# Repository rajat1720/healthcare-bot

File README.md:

# healthcare-bot
A bot that can record the temperature of every individual and send it to the doctors, so that they can filtrate the people who needs to go for the second level of testing for Covid-19

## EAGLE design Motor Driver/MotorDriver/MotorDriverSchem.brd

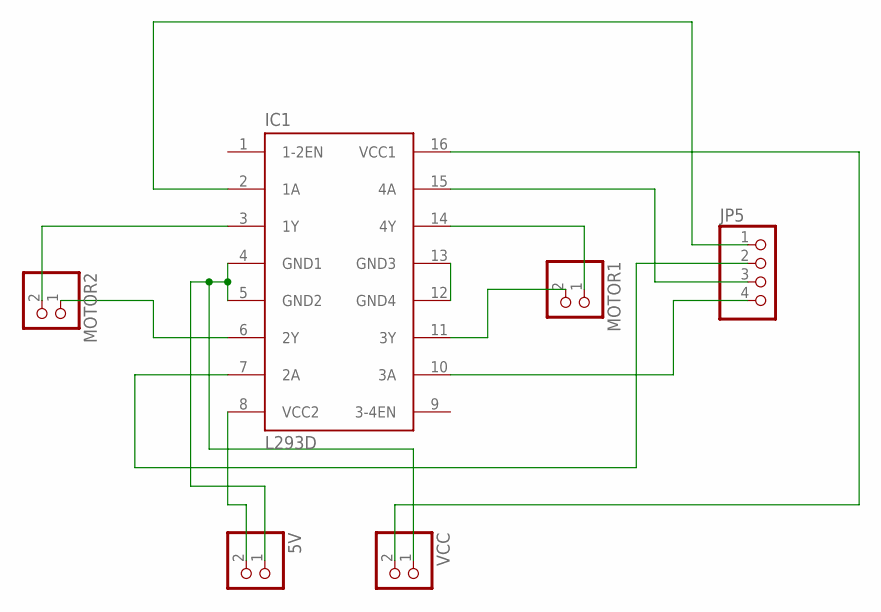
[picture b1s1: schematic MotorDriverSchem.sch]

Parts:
5V: PINHD-1X2; 1X02
IC1: L293D; DIL16
JP5: PINHD-1X4; 1X04
MOTOR1, MOTOR2: PINHD-1X2; 1X02
VCC: PINHD-1X2; 1X02

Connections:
unnamed: IC1.3 (1Y), MOTOR2.2
unnamed: IC1.6 (2Y), MOTOR2.1
unnamed: IC1.14 (4Y), MOTOR1.1
unnamed: IC1.11 (3Y), MOTOR1.2
unnamed: 5V.1, IC1.4 (GND1), IC1.5 (GND2), VCC.1
unnamed: IC1.12 (GND4), IC1.13 (GND3)
unnamed: IC1.2 (1A), JP5.1
unnamed: IC1.7 (2A), JP5.2
unnamed: IC1.15 (4A), JP5.3
unnamed: IC1.10 (3A), JP5.4
unnamed: 5V.2, IC1.8 (VCC2)
unnamed: IC1.16 (VCC1), VCC.2

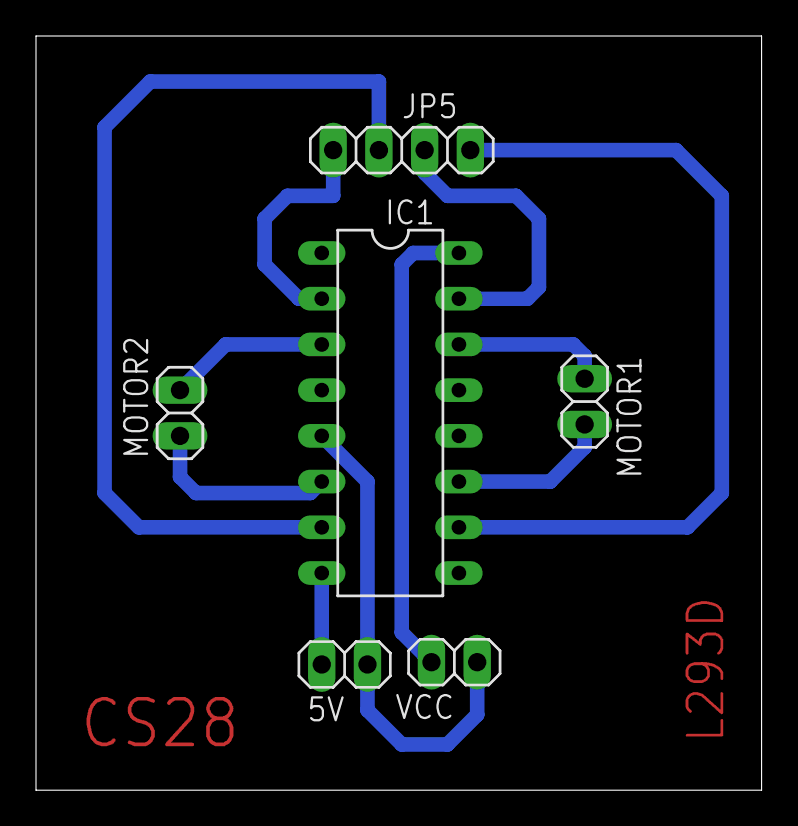
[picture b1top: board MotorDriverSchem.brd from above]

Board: 2 copper layers, 40.3 x 41.9 mm, 6 parts (0 on the bottom side), 12 nets.

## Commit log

2020-04-12 Create Hardware-used
2020-04-12 Create Software-used
2020-06-19 Create Motor Driver
2020-06-19 Create App
